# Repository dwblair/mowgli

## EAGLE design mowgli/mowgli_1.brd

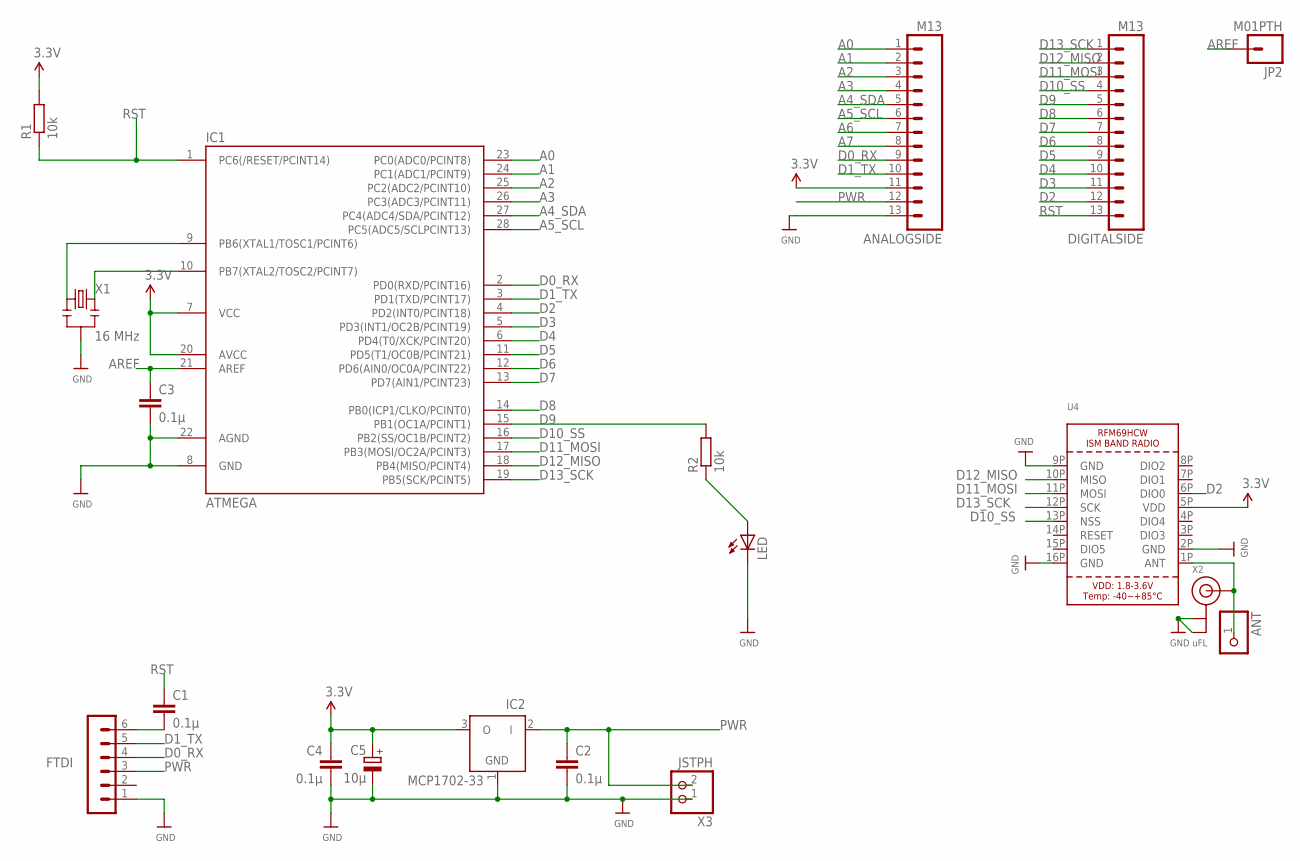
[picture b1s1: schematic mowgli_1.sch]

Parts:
ANALOGSIDE: M13; 1X13
ANT: HEADER-1X1ROUND; 1X01_ROUND
C1, C2, C3, C4: 0.1µ; C025-024X044
C5: 10µ; E1,8-4
DIGITALSIDE: M13; 1X13
FTDI: FTDI; MA06-1
IC1: ATMEGA; DIL28-3
IC2: MCP1702-33; TO92
JP2: M01PTH; 1X01
LED: LED3MM
R1, R2: 10k; 0204/7
U4: RFM69HCW_SMT; RFMHCW_SMT
X1: 16 MHz; RESONATOR-PTH
X2: uFL; U.FL
X3: JSTPH; JSTPH2

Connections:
A0: ANALOGSIDE.1, IC1.23 (PC0(ADC0/PCINT8))
A1: ANALOGSIDE.2, IC1.24 (PC1(ADC1/PCINT9))
A2: ANALOGSIDE.3, IC1.25 (PC2(ADC2/PCINT10))
A3: ANALOGSIDE.4, IC1.26 (PC3(ADC3/PCINT11))
A4_SDA: ANALOGSIDE.5, IC1.27 (PC4(ADC4/SDA/PCINT12))
A5_SCL: ANALOGSIDE.6, IC1.28 (PC5(ADC5/SCLPCINT13))
A6: ANALOGSIDE.7
A7: ANALOGSIDE.8
ANT: ANT.1, U4.1P (ANT), X2.3 (SIGNAL)
AREF: C3.1, IC1.21 (AREF), JP2.1
D0_RX: ANALOGSIDE.9, FTDI.4, IC1.2 (PD0(RXD/PCINT16))
D1_TX: ANALOGSIDE.10, FTDI.5, IC1.3 (PD1(TXD/PCINT17))
D2: DIGITALSIDE.12, IC1.4 (PD2(INT0/PCINT18)), U4.6P (DIO0)
D3: DIGITALSIDE.11, IC1.5 (PD3(INT1/OC2B/PCINT19))
D4: DIGITALSIDE.10, IC1.6 (PD4(T0/XCK/PCINT20))
D5: DIGITALSIDE.9, IC1.11 (PD5(T1/OC0B/PCINT21))
D6: DIGITALSIDE.8, IC1.12 (PD6(AIN0/OC0A/PCINT22))
D7: DIGITALSIDE.7, IC1.13 (PD7(AIN1/PCINT23))
D8: DIGITALSIDE.6, IC1.14 (PB0(ICP1/CLKO/PCINT0))
D9: DIGITALSIDE.5, IC1.15 (PB1(OC1A/PCINT1)), R2.2
D10_SS: DIGITALSIDE.4, IC1.16 (PB2(SS/OC1B/PCINT2)), U4.13P (NSS)
D11_MOSI: DIGITALSIDE.3, IC1.17 (PB3(MOSI/OC2A/PCINT3)), U4.11P (MOSI)
D12_MISO: DIGITALSIDE.2, IC1.18 (PB4(MISO/PCINT4)), U4.10P (MISO)
D13_SCK: DIGITALSIDE.1, IC1.19 (PB5(SCK/PCINT5)), U4.12P (SCK)
GND: ANALOGSIDE.13, C2.2, C3.2, C4.2, C5.-, FTDI.1, IC1.8 (GND), IC1.22 (AGND), IC2.1 (GND), LED.K (C), U4.2P (GND), U4.9P (GND), U4.16P (GND), X1.2, X2.1 (GND), X2.2 (GND), X3.1
unnamed: IC1.9 (PB6(XTAL1/TOSC1/PCINT6)), X1.1
unnamed: LED.A, R2.1
unnamed: C1.2, FTDI.6
unnamed: IC1.10 (PB7(XTAL2/TOSC2/PCINT7)), X1.3
PWR: ANALOGSIDE.12, C2.1, FTDI.3, IC2.2 (I), X3.2
RST: C1.1, DIGITALSIDE.13, IC1.1 (PC6(/RESET/PCINT14)), R1.1
VCC: ANALOGSIDE.11, C4.1, C5.+, IC1.7 (VCC), IC1.20 (AVCC), IC2.3 (O), R1.2, U4.5P (VDD)

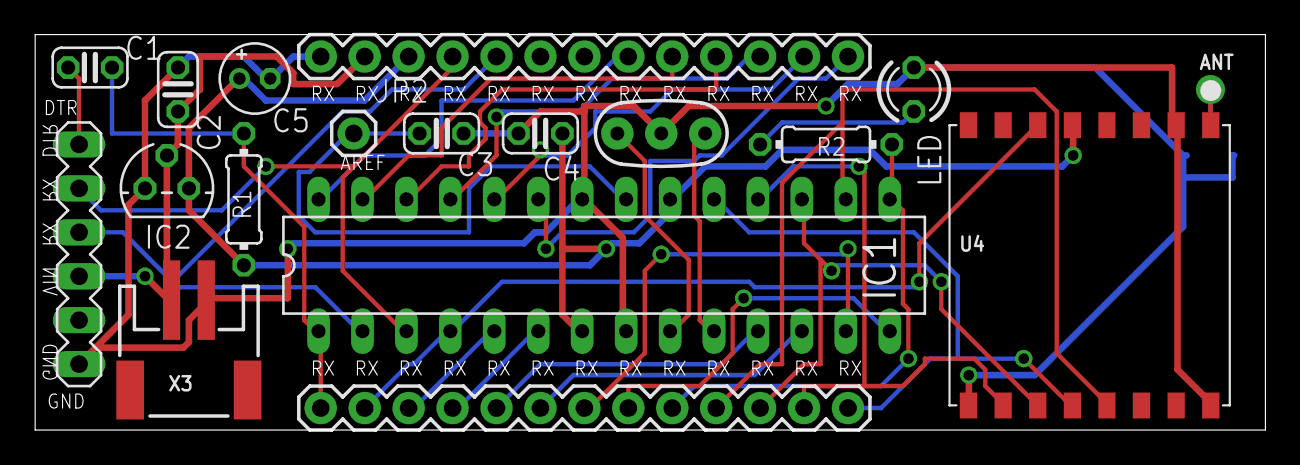
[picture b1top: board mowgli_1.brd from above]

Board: 2 copper layers, 71.2 x 22.9 mm, 19 parts (1 on the bottom side), 30 nets.

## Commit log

2016-09-06 upddate

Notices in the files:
parts and their libraries:
SparkFun-Connectors: Licensing: CC v3.0 Share-Alike You are welcome to use this library for commercial purposes.
microbuilder: This work is placed in the public domain, and may be freely used for commercial and non-commercial work with the following conditions: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
